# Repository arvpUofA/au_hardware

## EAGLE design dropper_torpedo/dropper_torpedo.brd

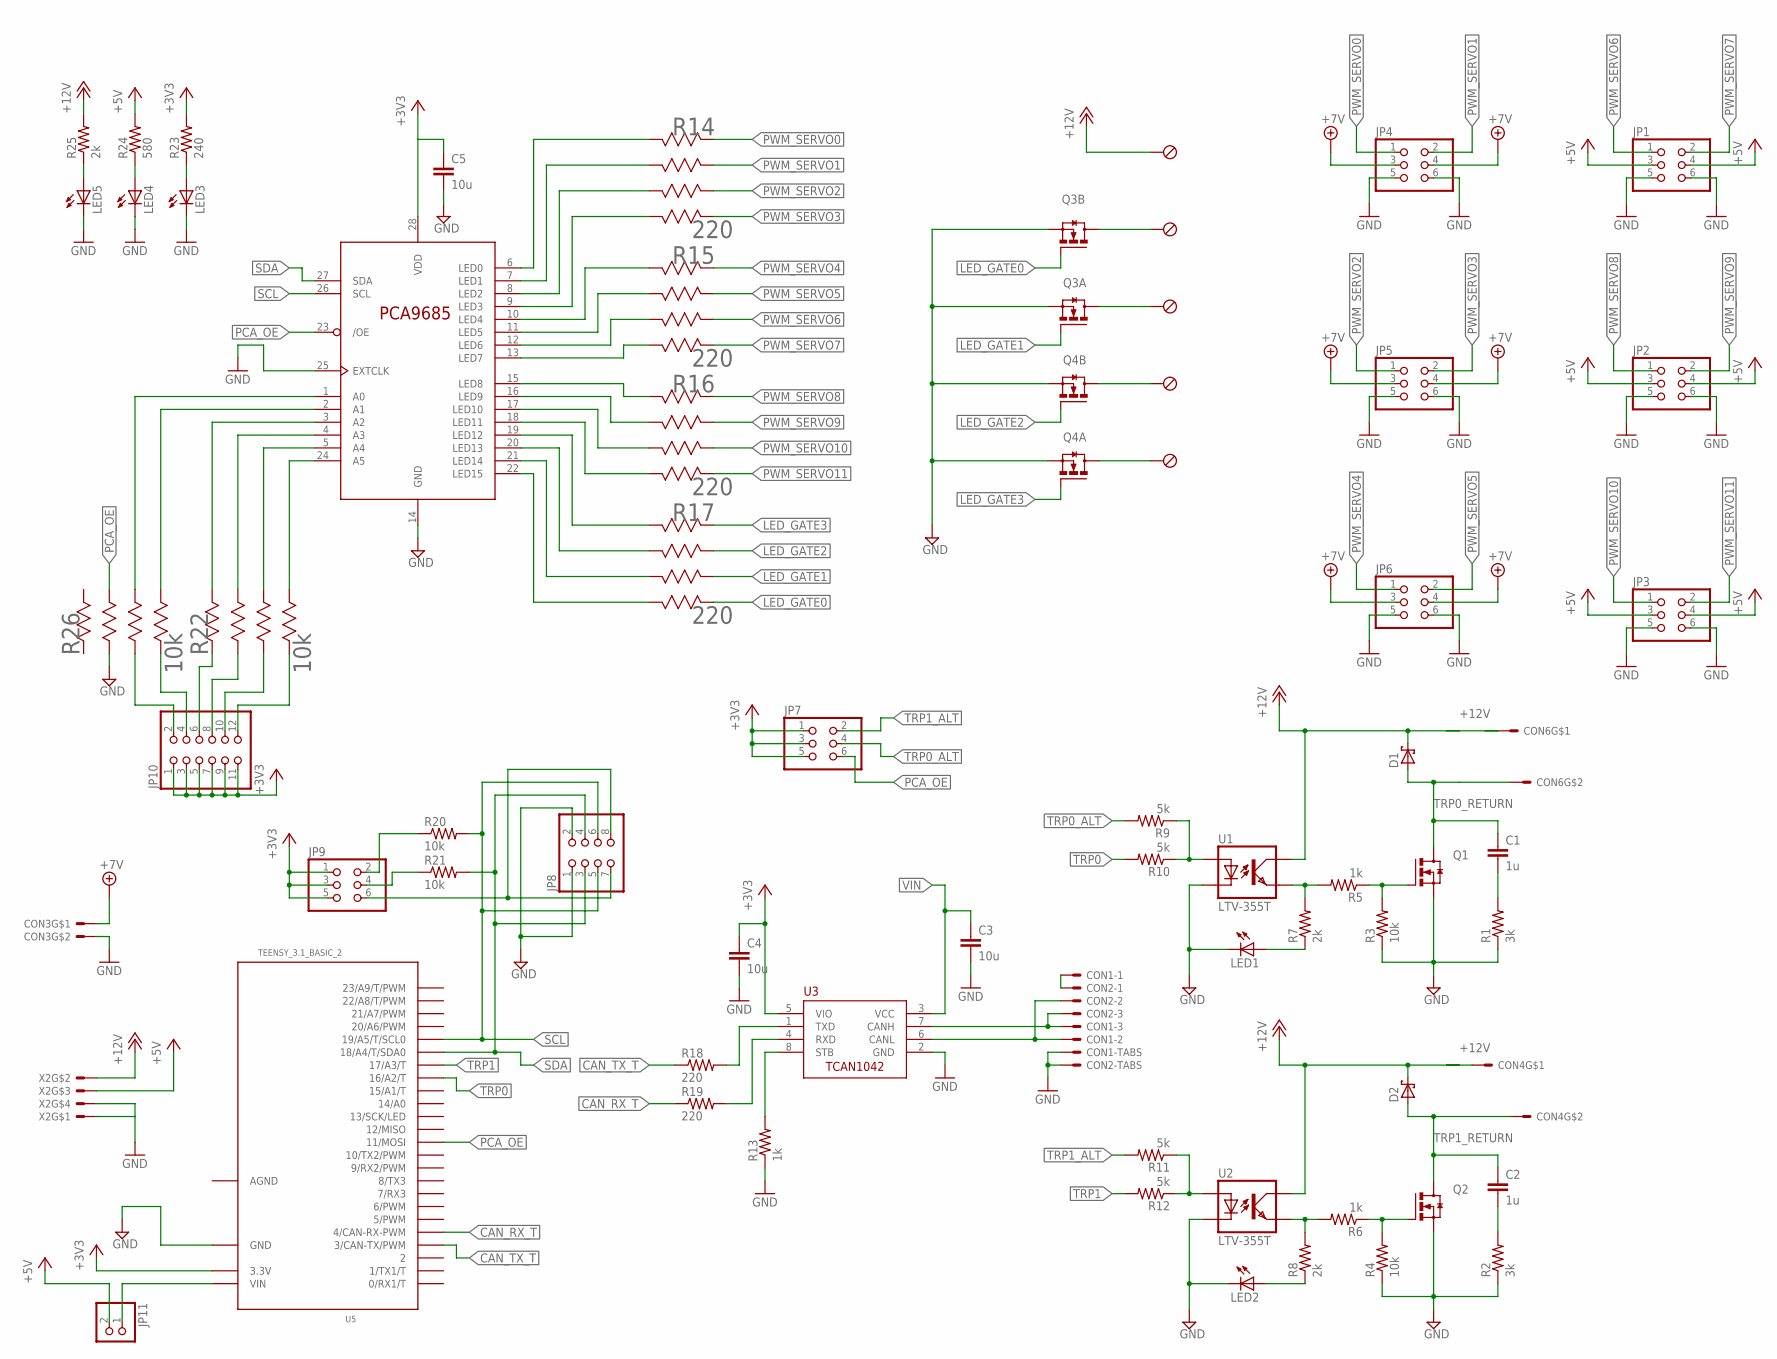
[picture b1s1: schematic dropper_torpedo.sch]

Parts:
C1, C2: 1u; C1206
C3, C4, C5: 10u; C0805
CON1, CON2: SM03B-GHS-TB
CON3, CON4, CON6: MOLEX_5566-2; 5566-2
D1, D2: STPS1L30A; DO214AC
JP1, JP2, JP3, JP4, JP5, JP6, JP7, JP9: PINHD-2X3; 2X03
JP8: PINHD-2X4; 2X04
JP10: PINHD-2X6; 2X06
JP11: PINHD-1X2; 1X02
LED1, LED2, LED3, LED4, LED5: LEDCHIPLED_1206; CHIPLED_1206
Q1, Q2: SI4896DY-T1-E3; SO-8
Q3, Q4: IRL6372TRPBF; SO-8
R1, R2: 3k; R1206
R3, R4, R20, R21: 10k; R1206
R5, R6: 1k; R1206
R7, R8, R25: 2k; R1206
R9, R10, R11, R12: 5k; R0805
R13: 1k; R0805
R14, R15, R16, R17: 220; EXBV8V-M
R18, R19: 220; R0805
R22, R26: 10k; EXBV8V-M
R23: 240; R1206
R24: 580; R1206
U1, U2: LTV-355T; SMD4
U3: TCAN1042HVDR; SO-8
U4: PCA9685PW; TSSOP28
U5: TEENSY_3.1_BASIC_2
X1: OSTVN05A150
X2: MOLEX_5566-4; 5566-4

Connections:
+3V3: C4.1, C5.1, JP7.1, JP7.3, JP7.5, JP9.1, JP9.3, JP9.5, JP10.1, JP10.3, JP10.5, JP10.7, JP10.9, JP10.11, R23.2, U3.5 (VIO), U4.28 (VDD), U5.3.3V
+5V: JP1.3, JP1.4, JP2.3, JP2.4, JP3.3, JP3.4, JP11.2, R24.2, X2.3
+7V: CON3.1, JP4.3, JP4.4, JP5.3, JP5.4, JP6.3, JP6.4
+12V: CON4.1, CON6.1, D1.C, D2.C, R25.2, U1.COLLECTOR (COL), U2.COLLECTOR (COL), X1.P$5, X2.2
A0: R26.6 (66), U4.1 (A0)
A0+: JP10.2, R26.3 (35)
A1: R26.5 (58), U4.2 (A1)
A1+: JP10.4, R26.4 (47)
A2: R22.8 (82), U4.3 (A2)
A2+: JP10.6, R22.1 (11)
A3: R22.7 (74), U4.4 (A3)
A3+: JP10.8, R22.2 (23)
A4: R22.6 (66), U4.5 (A4)
A4+: JP10.10, R22.3 (35)
A5: R22.5 (58), U4.24 (A5)
A5+: JP10.12, R22.4 (47)
AGND: U5.AGND
CANH: CON1.P$3, CON2.P$3, U3.7 (CANH)
CANL: CON1.P$2, CON2.P$2, U3.6 (CANL)
CANSH: CON1.P$1, CON2.P$1
CAN_RX: R19.2, U3.4 (RXD)
CAN_RX_T: R19.1, U5.4 (4/CAN-RX-PWM)
CAN_TX1: R18.2, U3.1 (TXD)
CAN_TX_T: R18.1, U5.3 (3/CAN-TX/PWM)
GND: C3.2, C4.2, C5.2, CON1.P$4, CON1.P$5, CON2.P$4, CON2.P$5, CON3.2, JP1.5, JP1.6, JP2.5, JP2.6, JP3.5, JP3.6, JP4.5, JP4.6, JP5.5, JP5.6, JP6.5, JP6.6, JP8.1, JP8.2, LED1.C, LED2.C, LED3.C, LED4.C, LED5.C, Q1.1 (S), Q1.2 (S), Q1.3 (S), Q2.1 (S), Q2.2 (S), Q2.3 (S), Q3.1 (S), Q3.3 (S), Q4.1 (S), Q4.3 (S), R1.1, R2.1, R3.1, R4.1, R13.1, R26.2 (23), U1.CATHODE (C), U2.CATHODE (C), U3.2 (GND), U4.14 (GND), U4.25 (EXTCLK), U5.GND, X2.1, X2.4
I2C_3V3: JP8.7, JP8.8, JP9.6
LED_DRAIN0: Q3.7 (D), Q3.8 (D), X1.P$4
LED_DRAIN1: Q3.5 (D), Q3.6 (D), X1.P$3
LED_DRAIN2: Q4.7 (D), Q4.8 (D), X1.P$2
LED_DRAIN3: Q4.5 (D), Q4.6 (D), X1.P$1
LED_GATE0: Q3.2 (G), R17.4 (47)
LED_GATE1: Q3.4 (G), R17.3 (35)
LED_GATE2: Q4.2 (G), R17.2 (23)
LED_GATE3: Q4.4 (G), R17.1 (11)
unnamed: LED1.A, R7.1
unnamed: LED2.A, R8.1
unnamed: LED3.A, R23.1
unnamed: LED4.A, R24.1
unnamed: LED5.A, R25.1
PCA_OE: JP7.6, R26.7 (74), U4.23 (/OE), U5.11 (11/MOSI)
PWM_CH0: R14.8 (82), U4.6 (LED0)
PWM_CH1: R14.7 (74), U4.7 (LED1)
PWM_CH2: R14.6 (66), U4.8 (LED2)
PWM_CH3: R14.5 (58), U4.9 (LED3)
PWM_CH4: R15.8 (82), U4.10 (LED4)
PWM_CH5: R15.7 (74), U4.11 (LED5)
PWM_CH6: R15.6 (66), U4.12 (LED6)
PWM_CH7: R15.5 (58), U4.13 (LED7)
PWM_CH8: R16.8 (82), U4.15 (LED8)
PWM_CH9: R16.7 (74), U4.16 (LED9)
PWM_CH10: R16.6 (66), U4.17 (LED10)
PWM_CH11: R16.5 (58), U4.18 (LED11)
PWM_CH12: R17.8 (82), U4.19 (LED12)
PWM_CH13: R17.7 (74), U4.20 (LED13)
PWM_CH14: R17.6 (66), U4.21 (LED14)
PWM_CH15: R17.5 (58), U4.22 (LED15)
PWM_SERVO0: JP4.1, R14.1 (11)
PWM_SERVO1: JP4.2, R14.2 (23)
PWM_SERVO2: JP5.1, R14.3 (35)
PWM_SERVO3: JP5.2, R14.4 (47)
PWM_SERVO4: JP6.1, R15.1 (11)
PWM_SERVO5: JP6.2, R15.2 (23)
PWM_SERVO6: JP1.1, R15.3 (35)
PWM_SERVO7: JP1.2, R15.4 (47)
PWM_SERVO8: JP2.1, R16.1 (11)
PWM_SERVO9: JP2.2, R16.2 (23)
PWM_SERVO10: JP3.1, R16.3 (35)
PWM_SERVO11: JP3.2, R16.4 (47)
RC0: C1.2, R1.2
RC1: C2.2, R2.2
SCL: JP8.5, JP8.6, R20.2, U4.26 (SCL), U5.19/A5 (19/A5/T/SCL0)
SCL_3V3: JP9.2, R20.1
SDA: JP8.3, JP8.4, R21.2, U4.27 (SDA), U5.18/A4 (18/A4/T/SDA0)
SDA_3V3: JP9.4, R21.1
STB: R13.2, U3.8 (STB)
TOPTO_A0: R9.1, R10.1, U1.ANODE (A)
TOPTO_A1: R11.1, R12.1, U2.ANODE (A)
TOPTO_E0: R5.2, R7.2, U1.EMITTER (EMIT)
TOPTO_E1: R6.2, R8.2, U2.EMITTER (EMIT)
TRP0: R10.2, U5.16/A2 (16/A2/T)
TRP0_ALT: JP7.4, R9.2
TRP0_RETURN: CON6.2
TRP1: R12.2, U5.17/A3 (17/A3/T)
TRP1_ALT: JP7.2, R11.2
TRP1_RETURN: C2.1, CON4.2, D2.A, Q2.5 (D), Q2.6 (D), Q2.7 (D), Q2.8 (D)
TRP_GATE0: Q1.4 (G), R3.2, R5.1
TRP_GATE1: Q2.4 (G), R4.2, R6.1
TRP_RETURN0: C1.1, D1.A, Q1.5 (D), Q1.6 (D), Q1.7 (D), Q1.8 (D)
VIN: C3.1, JP11.1, U3.3 (VCC), U5.VIN

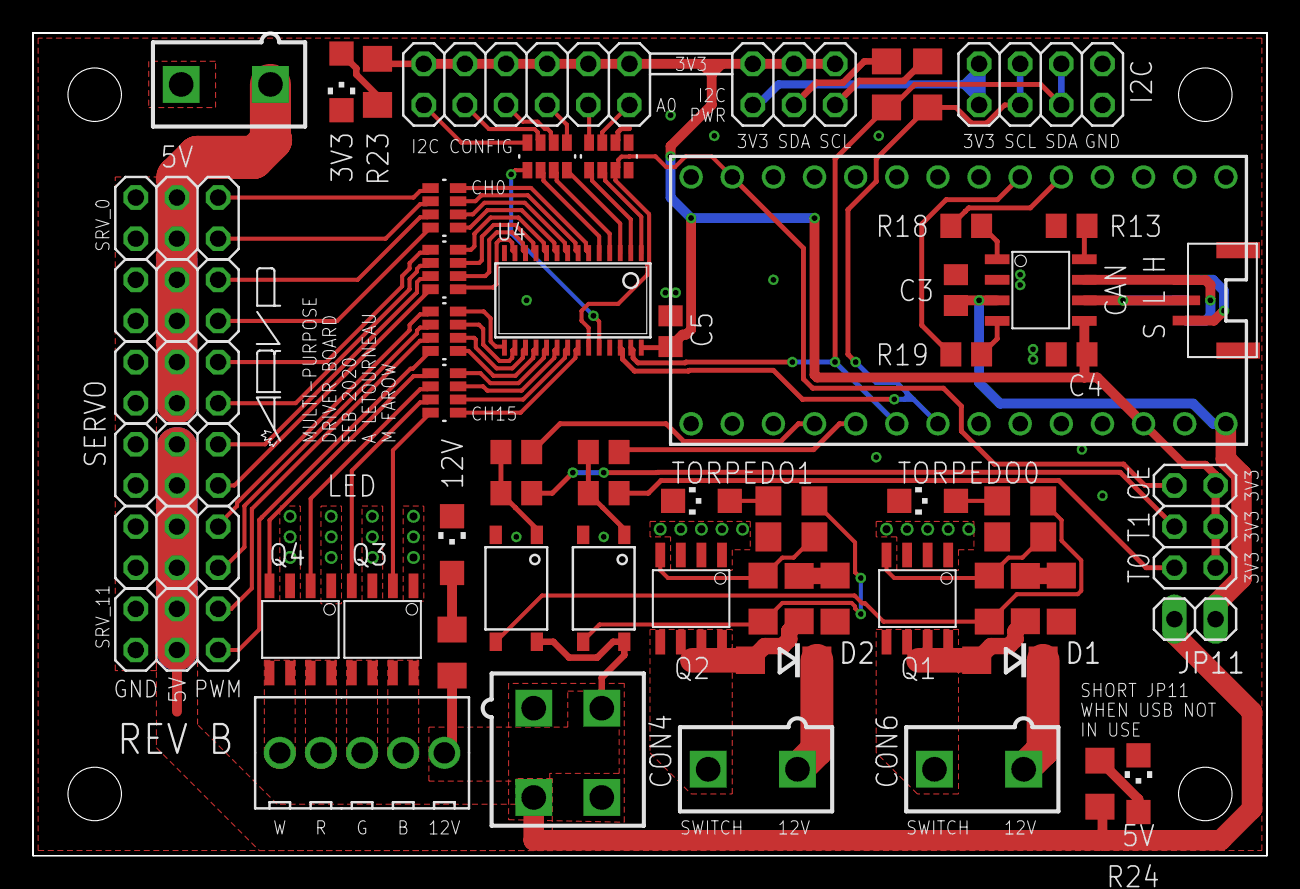
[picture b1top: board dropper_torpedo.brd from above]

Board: 2 copper layers, 76.2 x 50.8 mm, 72 parts (1 on the bottom side), 87 nets.

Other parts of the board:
U$5: LOGO3
U$6: LETTER_L
U$7: DOCFIELD
U$8, U$9, U$10, U$11: STAND-OFF

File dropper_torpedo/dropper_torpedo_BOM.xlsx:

Torpedo Board V3: Bill of Materials
Shematic Reference Number | Part Description | Manufacturer Part Number | Datasheet | Price | Quantity | Total Cost | Customer Reference
Q1, Q2 | MOSFET N-CH 80V 6.7A 8-SOIC | SI4896DY-T1-E3 | http://www.vishay.com/docs/71300/71300.pdf | 2.37 | 2 | 4.74 | DROP_TORP
Q3, Q4 | MOSFET 2N-CH 30V 8.1A 8SOIC | IRL6372TRPBF | http://www.infineon.com/dgdl/irl6372pbf.pdf?fileId=5546d4625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 | 1.15 | 2 | 2.3 | DROP_TORP
D1, D2 | DIODE SCHOTTKY 30V 1A SMA | STPS1L30A | http://www.st.com/content/ccc/resource/technical/document/da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 | 0.53 | 2 | 1.06 | DROP_TORP
U1, U2 | OPTOISO 3.75KV DARLINGTON 4SOP | LTV-355T | http://optoelectronics.liteon.com/upload/download/DS70-2001-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 | 0.74 | 2 | 1.48 | DROP_TORP
TRM1, TRM2 | TERM BLOCK 5.08MM HORZ 2POS PCB | OSTTC022162 | http://www.on-shore.com/wp-content/uploads/2015/09/osttcxx2162.pdf | 1.08 | 2 | 2.16 | DROP_TORP
LED1-5 | LED GREEN CLEAR 1206 SMD | LTST-C150GKT | http://optoelectronics.liteon.com/upload/download/DS-22-98-0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 | 0.46 | 2 | 0.92 | DROP_TORP
X2 | CONN HEADER 4POS 4.2MM VERT TIN | 39281043 | http://www.molex.com/pdm_docs/sd/039281043_sd.pdf | 1.04 | 1 | 1.04 | DROP_TORP
R14-17 | RES ARRAY 4 RES 220 OHM 1206 | EXB-V8V221JV | https://media.digikey.com/pdf/Data%20Sheets/Panasonic%20Resi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 | 0.14 | 4 | 0.56 | DROP_TORP
R22,26 | RES ARRAY 4 RES 10K OHM 1206 | EXB-V8V103JV | https://media.digikey.com/pdf/Data%20Sheets/Panasonic%20Resi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 | 0.14 | 2 | 0.28 | DROP_TORP
X1 | CONN TERM BLOCK 2.54MM 5POS PCB | OSTVN05A150 | http://www.on-shore.com/wp-content/uploads/2015/09/ostvnxxa150.pdf | 2.34 | 1 | 2.34 | DROP_TORP
C1,2 | CAP CER 1UF 50V X7R 1206 | CL31B105KBHNNNE | https://www.samsungsem.com/kr/support/product-search/mlcc/__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 | 0.26 | 2 | 0.52 | DROP_TORP
C3,4,5 | CAP CER 10UF 16V X7R 0805 | CL21B106KOQNNNG | http://www.samsungsem.com/kr/support/product-search/mlcc/CL2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 | 0.39 | 3 | 1.17 | DROP_TORP
R23 | RES SMD 240 OHM 1% 1/4W 1206 | RC1206FR-07240RL | http://www.yageo.com/documents/recent/PYu-RC_Group_51_RoHS_L_7.pdf | 0.047 | 1 | 0.047 | DROP_TORP
R24 | RES SMD 576 OHM 1% 1/4W 1206 | RC1206FR-07576RL | http://www.yageo.com/documents/recent/PYu-RC_Group_51_RoHS_L_7.pdf | 0.047 | 1 | 0.047 | DROP_TORP
R5,6 | RES SMD 1K OHM 1% 1/4W 1206 | RC1206FR-071KL | http://www.yageo.com/documents/recent/PYu-RC_Group_51_RoHS_L_7.pdf | 0.047 | 2 | 0.094 | DROP_TORP
R7,8,25 | RES SMD 2K OHM 1% 1/4W 1206 | RC1206FR-072KL | http://www.yageo.com/documents/recent/PYu-RC_Group_51_RoHS_L_7.pdf | 0.047 | 3 | 0.141 | DROP_TORP
R9-12 | RES SMD 4.99K OHM 1% 1/4W 0805 | RC0805FR-074K99L | http://www.yageo.com/documents/recent/PYu-RC_Group_51_RoHS_L_8.pdf | 0.031 | 4 | 0.124 | DROP_TORP
R18, 19 | RES SMD 220 OHM 1% 1/8W 0805 | RC0805FR-07220RL | http://www.yageo.com/documents/recent/PYu-RC_Group_51_RoHS_L_7.pdf | 0.031 | 2 | 0.062 | DROP_TORP
R1,2 | RES SMD 3K OHM 1% 1/4W 1206 | RC1206FR-073KL | http://www.yageo.com/documents/recent/PYu-RC_Group_51_RoHS_L_7.pdf | 0.047 | 2 | 0.094 | DROP_TORP
R3,4,20,21 | RES SMD 10K OHM 1% 1/4W 1206 | RC1206FR-0710KL | http://www.yageo.com/documents/recent/PYu-RC_Group_51_RoHS_L_7.pdf | 0.047 | 4 | 0.188 | DROP_TORP
R13 | RES SMD 1K OHM 1% 1/8W 0805 | RC0805FR-071KL | http://www.yageo.com/documents/recent/PYu-RC_Group_51_RoHS_L_7.pdf | 0.034 | 1 | 0.034 | DROP_TORP
U4 | IC LED DRIVER RGBA 28-TSSOP | PCA9685PW,118 | http://www.nxp.com/documents/data_sheet/PCA9685.pdf | 3.3 | 1 | 3.3 | DROP_TORP
Teensy 3.2 | CONN HEADER FMALE 14POS .1" GOLD | PPPC141LFBN-RC | http://www.sullinscorp.com/drawings/78_P(N)PxCxxxLFBN-RC,_10492-H.pdf | 1.28 | 2 | 2.56 | DROP_TORP
JP1-7,9,10 | DIL VERTICAL PC TAIL PIN HEADER 2x3 | M20-9980345 | https://cdn.harwin.com/pdfs/M20-998.pdf | 0.348 | 9 | 3.132 | DROP_TORP
JP8 | DIL VERTICAL PC TAIL PIN HEADER 2x4 | M20-9980445 | https://cdn.harwin.com/pdfs/M20-998.pdf | 0.48 | 1 | 0.48 | DROP_TORP
JP11 | SIL VERTICAL PC TAIL PIN HEADER 1x2 | M20-9990245 | https://cdn.harwin.com/pdfs/M20-999.pdf | 0.2 | 1 | 0.2 | DROP_TORP
U3 | IC TXRX CAN FAULT PROT 8SOIC | TCAN1042HVDRQ1 | http://www.ti.com/lit/ds/symlink/tcan1042hgv-q1.pdf | 2.05 | 1 | 2.05 | DROP_TORP
CON3 | CONN HEADER 2POS 4.2MM VERT TIN | 39281023 | http://www.molex.com/pdm_docs/sd/039281023_sd.pdf | 0.83 | 1 | 0.83 | DROP_TORP
CON1,2 | CONN HEADER GH SIDE 3POS 1.25MM | SM03B-GHS-TB(LF)(SN) | http://www.jst-mfg.com/product/pdf/eng/eGH.pdf | 0.68 | 2 | 1.36 | DROP_TORP
- | CONN JUMPER SHORTING GOLD FLASH | SPC02SYAN | http://www.sullinscorp.com/drawings/134_C02SYAN_11134.pdf | 0.083 | 9 | 0.747 | DROP_TORP
 |  |  |  |  | Total | 34.06

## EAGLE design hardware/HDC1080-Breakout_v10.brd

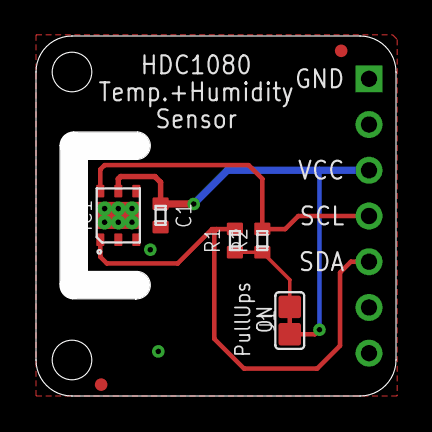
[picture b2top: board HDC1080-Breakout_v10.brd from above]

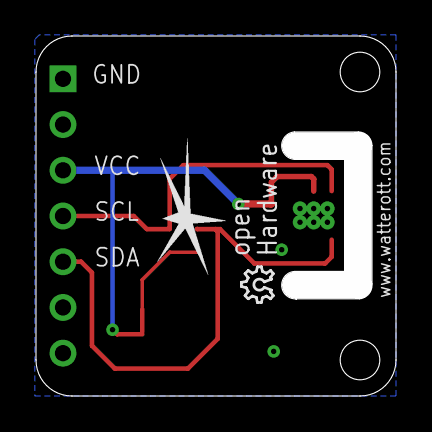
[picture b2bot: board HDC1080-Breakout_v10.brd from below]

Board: 2 copper layers, 20.0 x 20.0 mm, 10 parts (2 on the bottom side), 5 nets.

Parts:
B1: BREAKOUT-20X20
C1: 2u2; R0402
IC1: HDC1080; WSON6
J1: JUMPER2-0603
LOGO2: OSHW_LOGOX0070; OSHW_6X70
LOGO3: LOGO-S_PLACE_M; SPARK_TPLACE_M
R1, R2: 4k7; R0402
X1, X2: PASSER-07; PASSER_07MM

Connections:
GND: B1.GND, C1.1, IC1.2
unnamed: J1.1, R1.2, R2.2
SCL: B1.SCL/SCK, IC1.6, R2.1
SDA: B1.SDA/MISO, IC1.1, R1.1
VCC: B1.VCC, C1.2, IC1.5, J1.2

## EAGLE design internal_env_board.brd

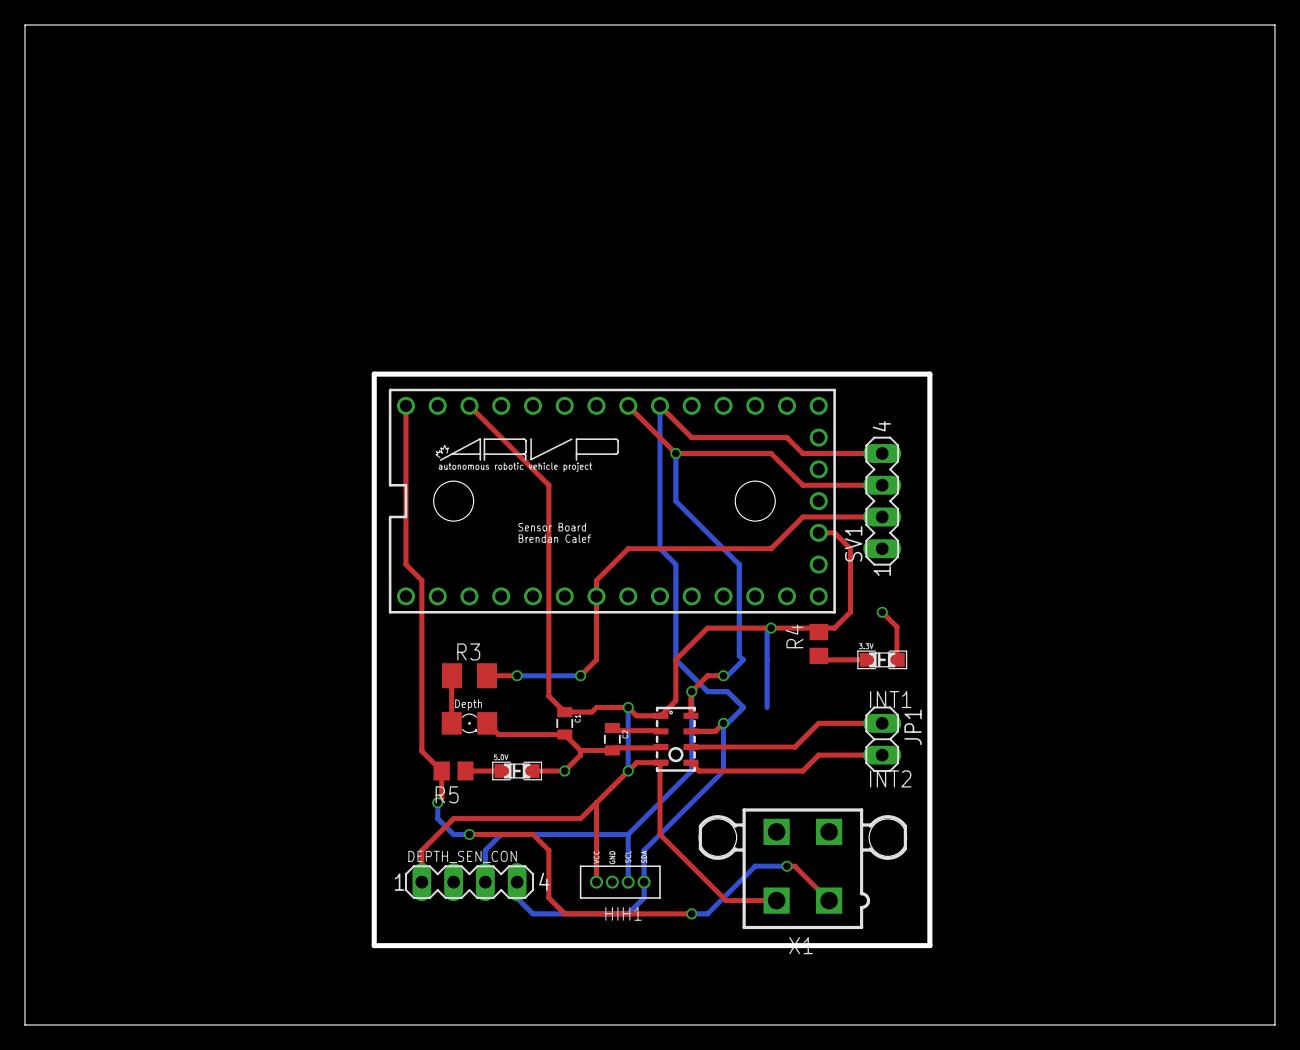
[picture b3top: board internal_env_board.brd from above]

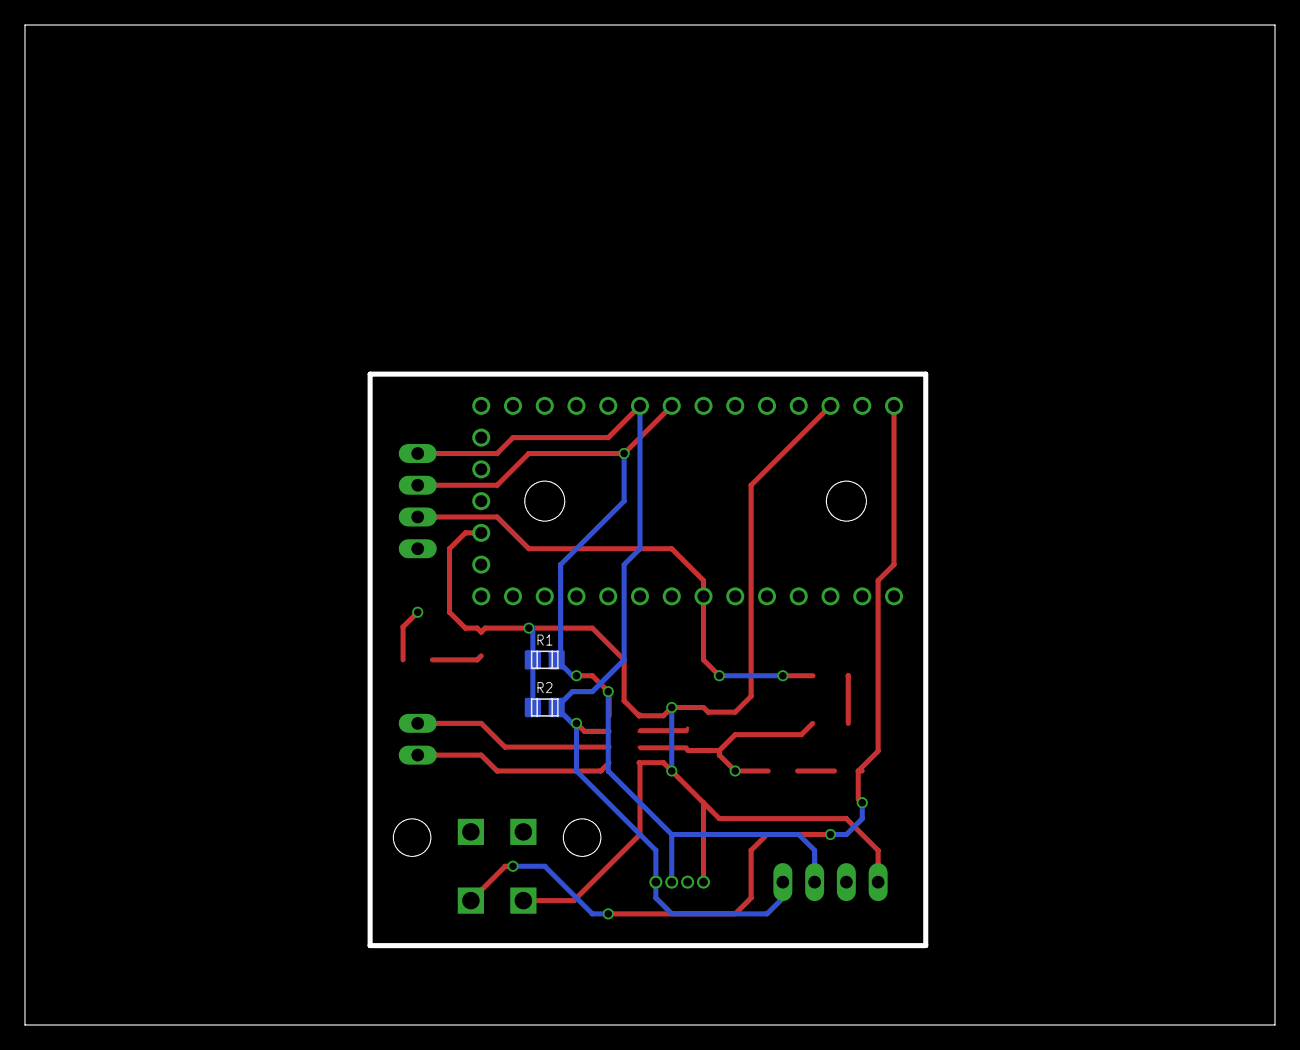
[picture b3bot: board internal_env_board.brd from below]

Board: 2 copper layers, 100.0 x 80.0 mm, 18 parts (2 on the bottom side), 12 nets.

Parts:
3.3V, 5.0V: 0805.LED
C1: 10uF; 0805
C2: 0.1uF; 0805
DEPTH_SEN_CON: MA04-1
HIH1: HIH7120; SIP4
JP1: 1X02
LED1: LED_1206
R1, R2: 4k7; R0805
R3: M1206
R4, R5: R0805
SV1: MA04-1
U1: MPL3115A2LGA8; LGA8
U$1: ARVP
U$2: TEENSY_3.1_BASIC
X1: 5566-4

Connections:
3V3: C1.1, DEPTH_SEN_CON.1, HIH1.VCC, R1.2, R2.2, R4.2, U1.1, U1.4, U$2.3.3V, U$2.3.3V1, X1.2
GND: 3.3V.P$2, 5.0V.P$2, C1.2, C2.2, DEPTH_SEN_CON.2, HIH1.GND, LED1.C, SV1.1, U1.3, U$2.GND, U$2.GND1, X1.3
GPIO: R3.2, SV1.2, U$2.5
INT1: JP1.1, U1.6
INT2: JP1.2, U1.5
unnamed: C2.1, U1.2
unnamed: 5.0V.P$1, R5.1
unnamed: LED1.A, R3.1
unnamed: 3.3V.P$1, R4.1
SCL: DEPTH_SEN_CON.3, HIH1.SCL, R1.1, SV1.3, U1.8, U$2.19/A5
SDA: DEPTH_SEN_CON.4, HIH1.SDA, R2.1, SV1.4, U1.7, U$2.18/A4
VCC: R5.2, U$2.VIN, X1.1

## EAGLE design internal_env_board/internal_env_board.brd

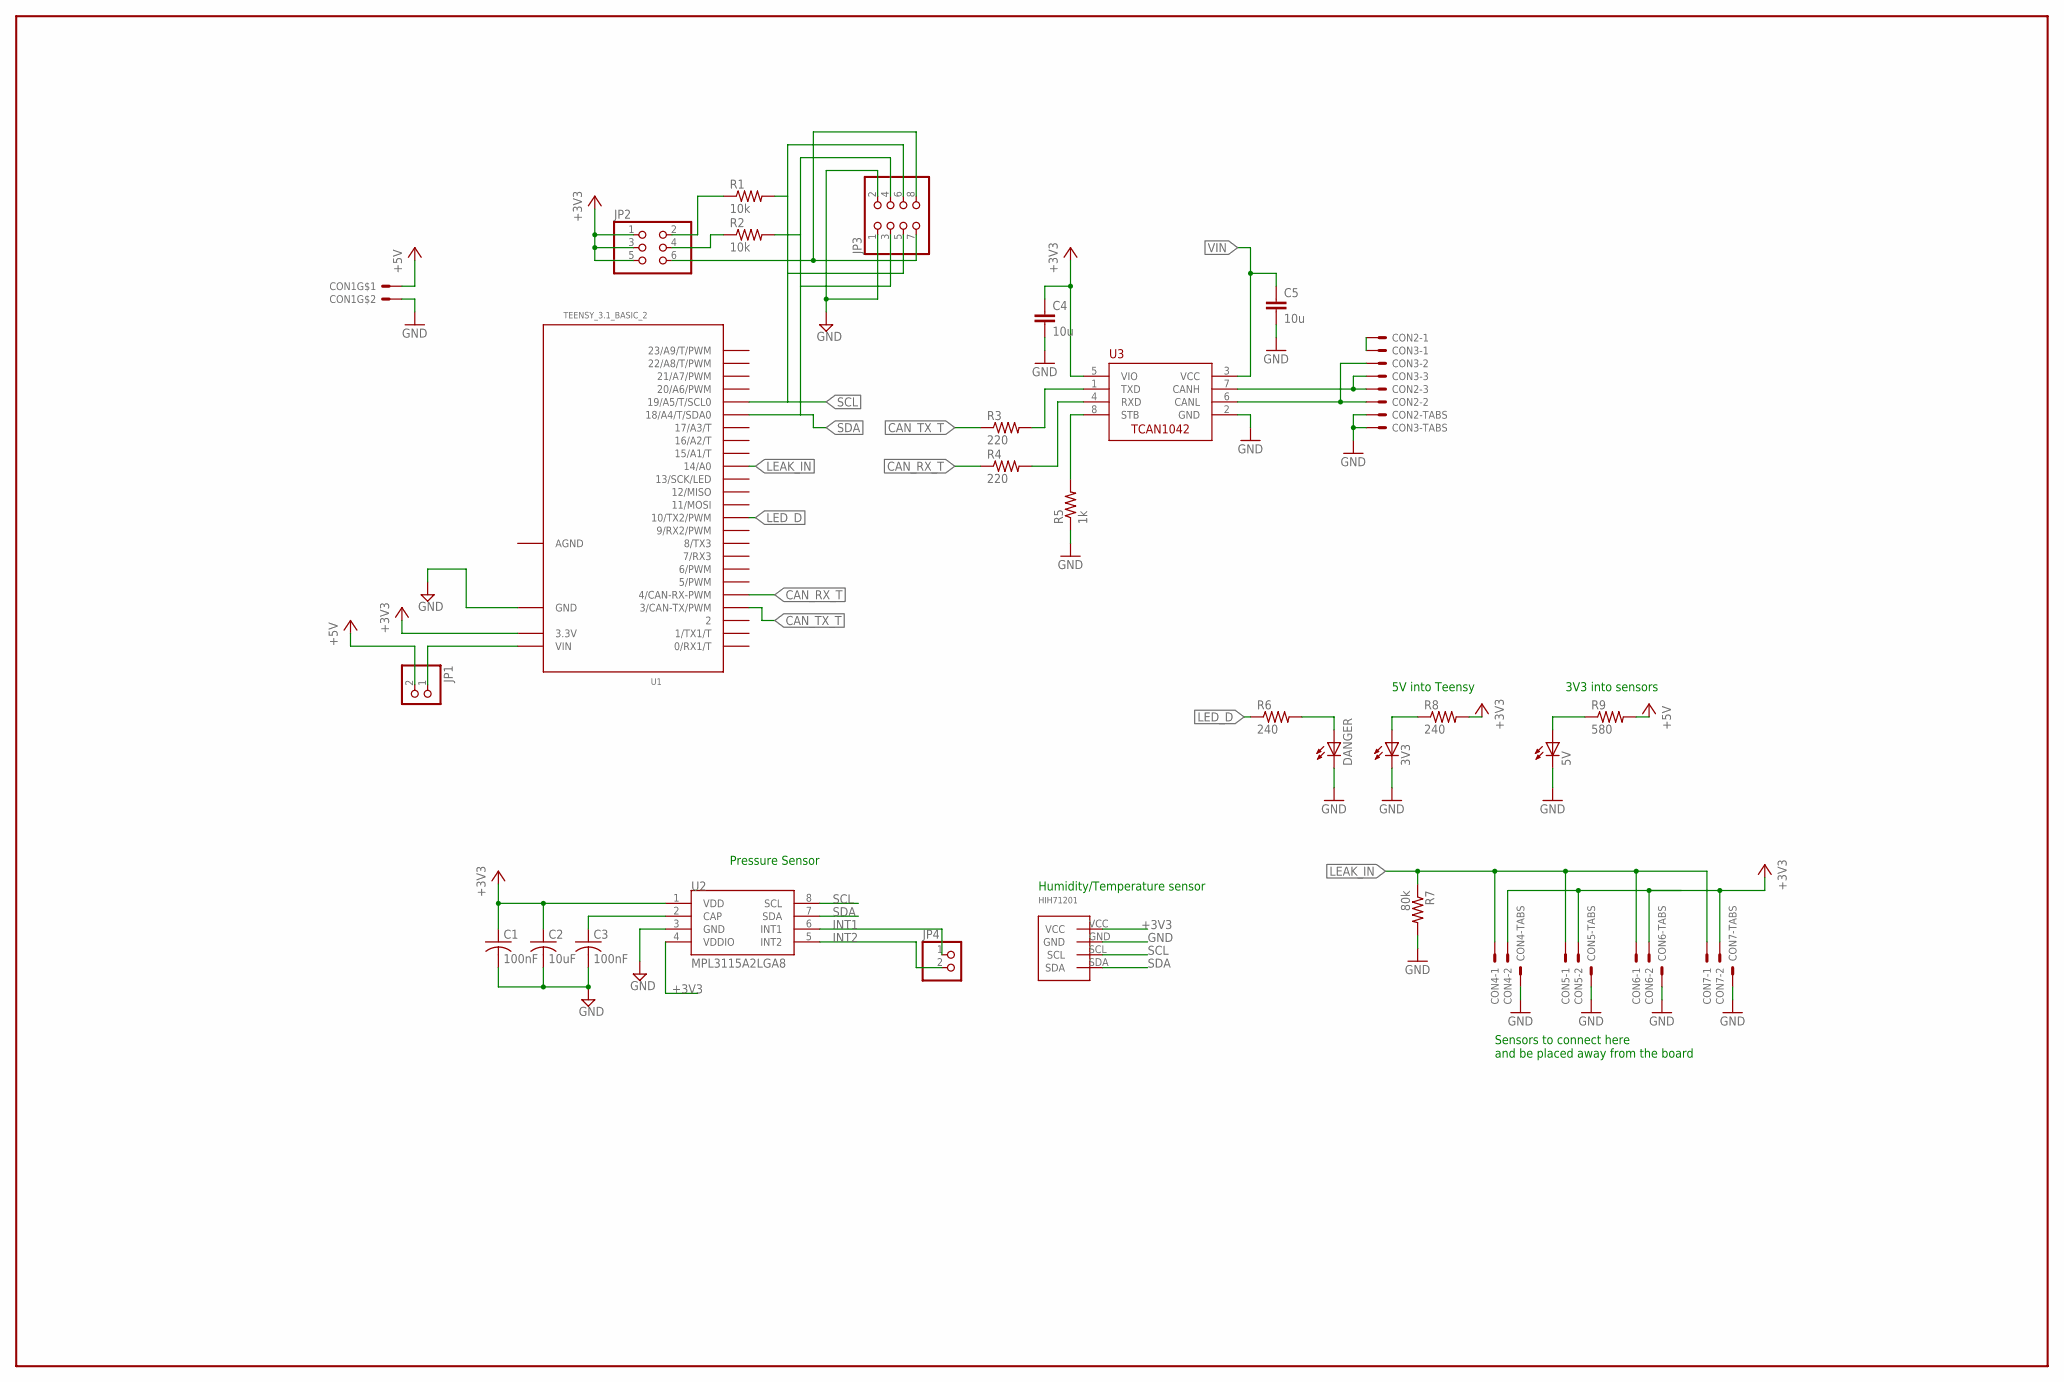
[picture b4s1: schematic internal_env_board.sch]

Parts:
3V3, 5V: LEDSMT1206; 1206
C1, C3: 100nF; C1206
C2: 10uF; C1206
C4, C5: 10u; C0805
CON1: MOLEX_5566-2; 5566-2
CON2, CON3: SM03B-GHS-TB
CON4, CON5, CON6, CON7: SM02B-GHS-TB
DANGER: LEDSMT1206; 1206
HIH71201: HIH7120; SIP4
JP1, JP4: PINHD-1X2; 1X02
JP2: PINHD-2X3; 2X03
JP3: PINHD-2X4; 2X04
R1, R2: 10k; R1206
R3, R4: 220; R0805
R5: 1k; R0805
R6, R8: 240; R1206
R7: 80k; R1206
R9: 580; R1206
U1: TEENSY_3.1_BASIC_2
U2: MPL3115A2LGA8; LGA8
U3: TCAN1042HVDR; SO-8

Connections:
+3V3: C1.1, C2.1, C4.1, CON4.P$2, CON5.P$2, CON6.P$2, CON7.P$2, HIH71201.VCC, JP2.1, JP2.3, JP2.5, R8.2, U1.3.3V, U2.1 (VDD), U2.4 (VDDIO), U3.5 (VIO)
+5V: CON1.1, JP1.2, R9.2
AGND: U1.AGND
CANH1: CON2.P$3, CON3.P$3, U3.7 (CANH)
CANL1: CON2.P$2, CON3.P$2, U3.6 (CANL)
CANSH1: CON2.P$1, CON3.P$1
CAN_RX1: R4.2, U3.4 (RXD)
CAN_RX_T: R4.1, U1.4 (4/CAN-RX-PWM)
CAN_TX2: R3.2, U3.1 (TXD)
CAN_TX_T: R3.1, U1.3 (3/CAN-TX/PWM)
CAP: C3.1, U2.2 (CAP)
GND: 3V3.C, 5V.C, C1.2, C2.2, C3.2, C4.2, C5.2, CON1.2, CON2.P$4, CON2.P$5, CON3.P$4, CON3.P$5, CON4.P$3, CON4.P$4, CON5.P$3, CON5.P$4, CON6.P$3, CON6.P$4, CON7.P$3, CON7.P$4, DANGER.C, HIH71201.GND, JP3.1, JP3.2, R5.1, R7.2, U1.GND, U2.3 (GND), U3.2 (GND)
I2C_3V1: JP2.6, JP3.7, JP3.8
INT1: JP4.1, U2.6 (INT1)
INT2: JP4.2, U2.5 (INT2)
LEAK_IN: CON4.P$1, CON5.P$1, CON6.P$1, CON7.P$1, R7.1, U1.14/A0
LED_D: R6.1, U1.10 (10/TX2/PWM)
unnamed: DANGER.A, R6.2
unnamed: 5V.A, R9.1
unnamed: 3V3.A, R8.1
SCL: HIH71201.SCL, JP3.5, JP3.6, R1.2, U1.19/A5 (19/A5/T/SCL0), U2.8 (SCL)
SCL_3V1: JP2.2, R1.1
SDA: HIH71201.SDA, JP3.3, JP3.4, R2.2, U1.18/A4 (18/A4/T/SDA0), U2.7 (SDA)
SDA_3V1: JP2.4, R2.1
STB1: R5.2, U3.8 (STB)
VIN: C5.1, JP1.1, U1.VIN, U3.3 (VCC)

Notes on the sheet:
Pressure Sensor
5V into Teensy
3V3 into sensors
Humidity/Temperature sensor
Sensors to connect here and be placed away from the board

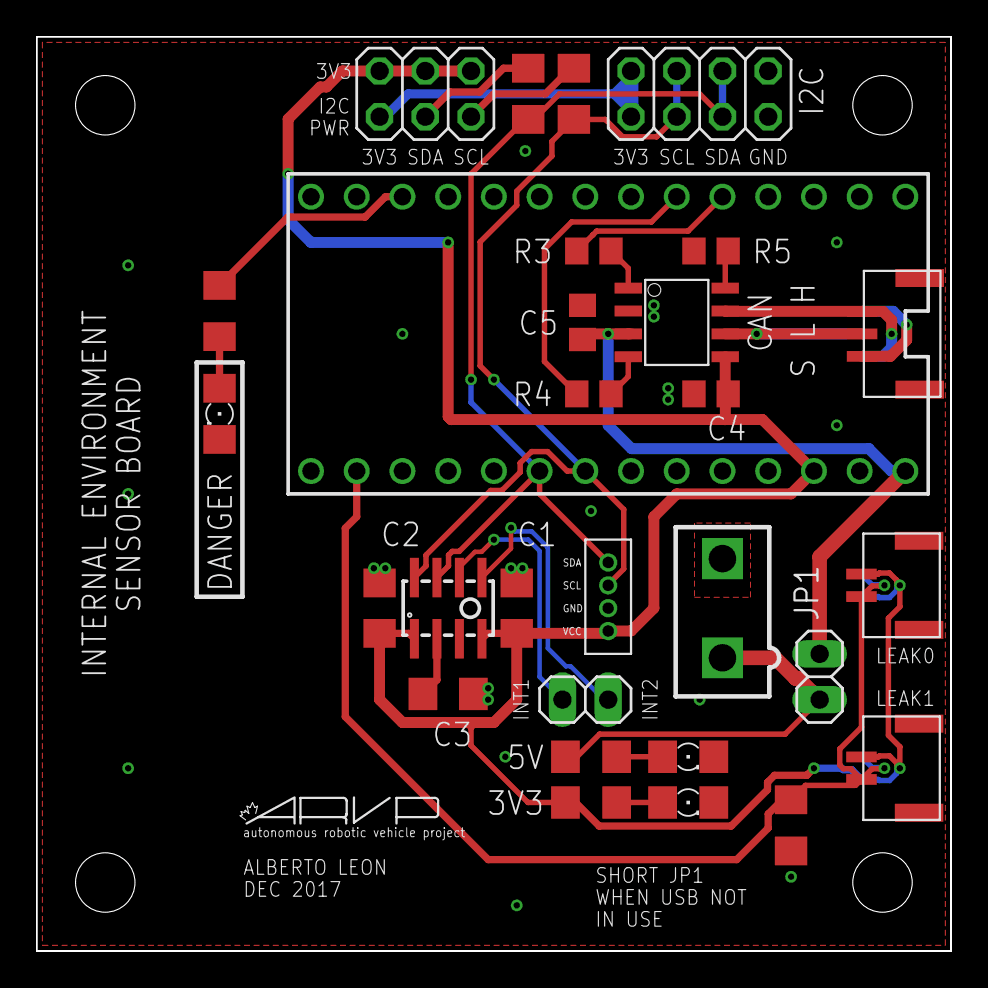
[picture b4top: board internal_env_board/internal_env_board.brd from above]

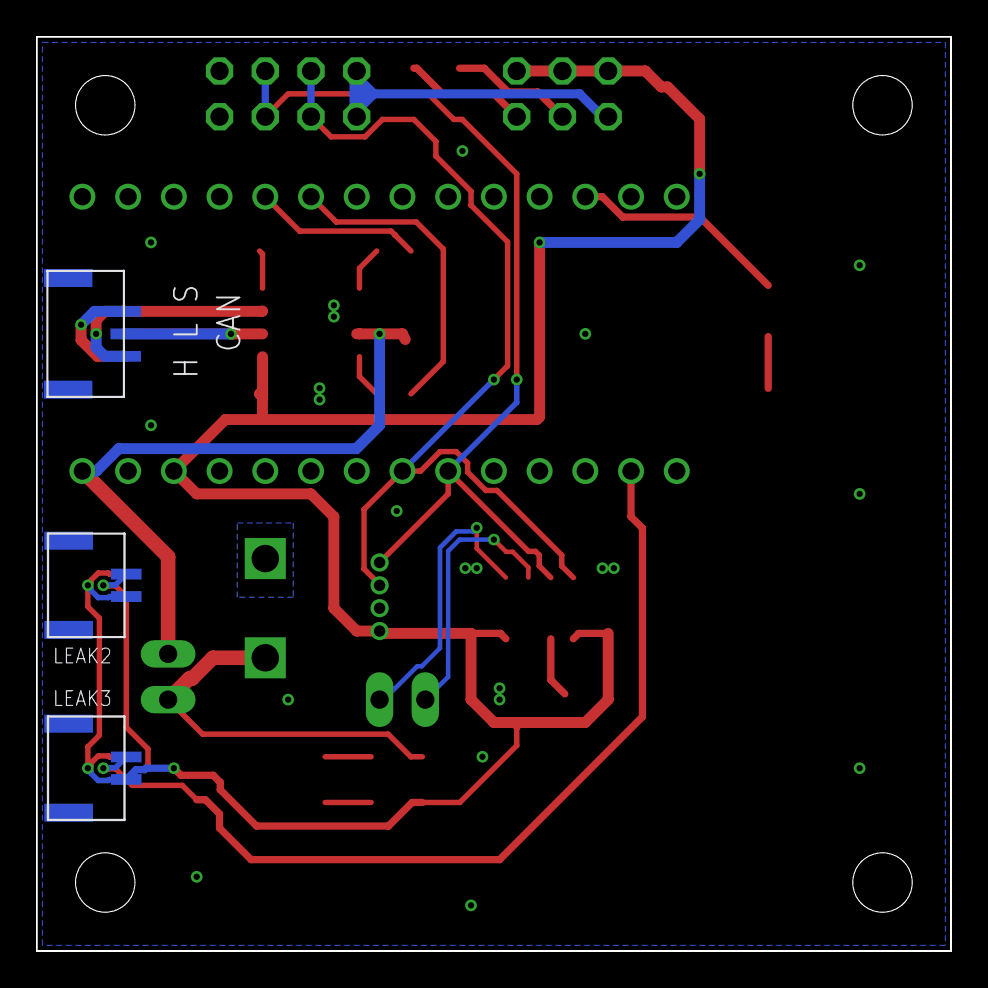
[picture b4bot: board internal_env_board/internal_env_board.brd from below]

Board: 2 copper layers, 50.8 x 50.8 mm, 39 parts (3 on the bottom side), 25 nets.

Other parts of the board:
U$1: LOGO2
U$2: LETTER_P
U$3: DOCFIELD
U$5, U$6, U$7, U$8: STAND-OFF

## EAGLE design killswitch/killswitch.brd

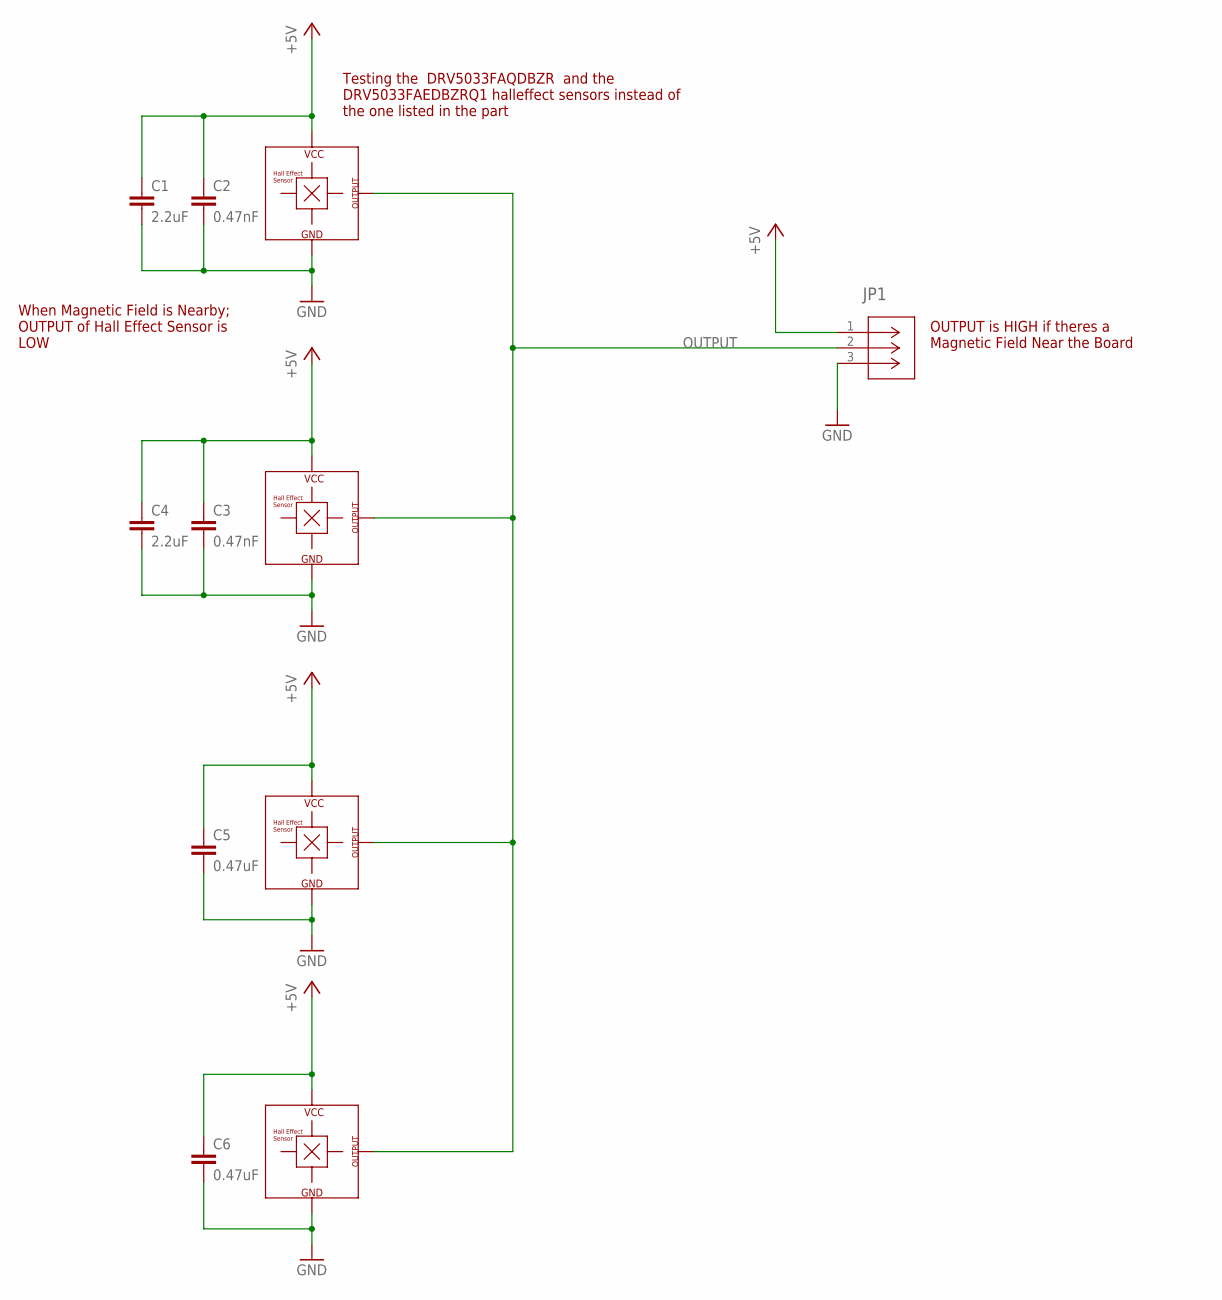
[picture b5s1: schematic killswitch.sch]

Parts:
C1, C4: 2.2uF; C0805
C2, C3: 0.47nF; C0603
C5, C6: 0.47uF; C0603
JP1: 1241150-3; CONN_1241150-3_TYCO
U$1, U$3, U$4, U$5: TCS40DLR; SOT23

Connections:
+5V: C1.1, C2.1, C3.1, C4.1, C5.1, C6.1, JP1.1, U$1.VCC, U$3.VCC, U$4.VCC, U$5.VCC
GND: C1.2, C2.2, C3.2, C4.2, C5.2, C6.2, JP1.3, U$1.GND, U$3.GND, U$4.GND, U$5.GND
OUTPUT: JP1.2, U$1.OUTPUT, U$3.OUTPUT, U$4.OUTPUT, U$5.OUTPUT

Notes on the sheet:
When Magnetic Field is Nearby; OUTPUT of Hall Effect Sensor is LOW
OUTPUT is HIGH if theres a Magnetic Field Near the Board
Testing the DRV5033FAQDBZR and the DRV5033FAEDBZRQ1 halleffect sensors instead of the one listed in the part

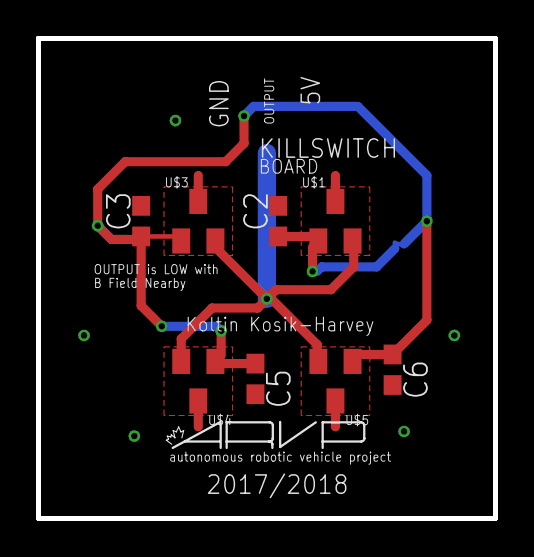
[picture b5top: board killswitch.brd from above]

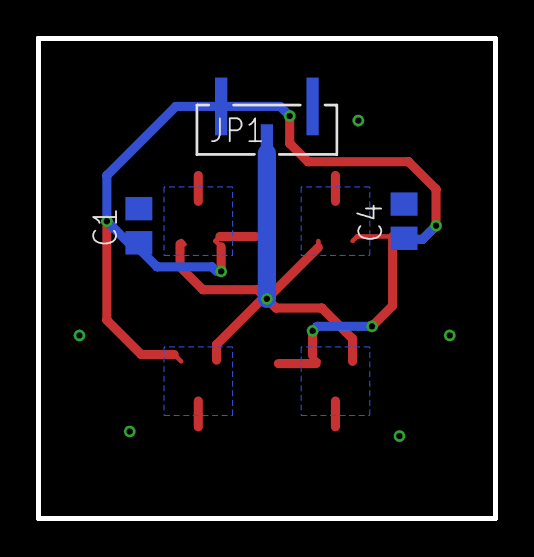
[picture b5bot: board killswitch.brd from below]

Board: 2 copper layers, 25.4 x 26.7 mm, 12 parts (3 on the bottom side), 3 nets.

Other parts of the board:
U$2: LOGO2

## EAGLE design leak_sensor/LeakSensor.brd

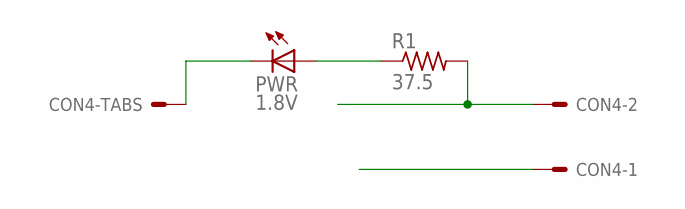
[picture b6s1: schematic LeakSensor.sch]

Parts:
CON4: SM02B-GHS-TB
PWR: 1.8V; 1206
R1: 37.5; R1206

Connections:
unnamed: PWR.A, R1.1
unnamed: CON4.P$3, CON4.P$4, PWR.C
PATH: CON4.P$1
PATH1: CON4.P$2, R1.2

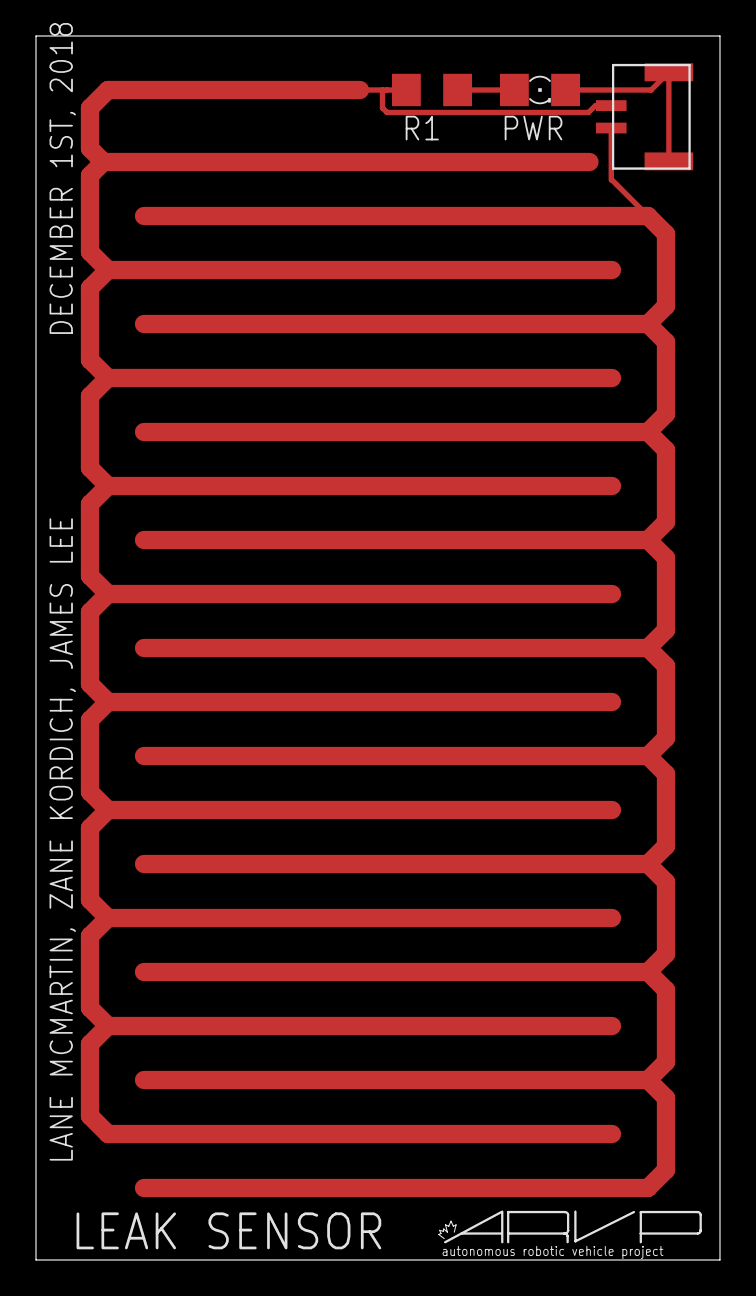
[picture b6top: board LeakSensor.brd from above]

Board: 2 copper layers, 38.0 x 68.0 mm, 4 parts (0 on the bottom side), 3 nets.

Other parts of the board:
U$1: ARVP

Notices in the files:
parts and their libraries:
SparkFun-Sensors: Licensing: CC v3.0 Share-Alike You are welcome to use this library for commercial purposes.
